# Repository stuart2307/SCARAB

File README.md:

# The SCARAB
The Save and Cartridge Aid Requiring Adapter Boards

# THE IDEA
As far as preservation goes, emphasis is placed on the software side of things.
Tools exist to dump ROMs, and archive them, but there are few tools to diagnose the hardware.
This is the niche the SCARAB aims to fill.

# WHAT DOES IT DO?
It tests the pins of cartridges to ensure they work correctly.
It validates the checksum of the internal ROM.
It tests the save battery, if applicable, via a Save Data Retention test.

# WHY DID YOU MAKE IT?
I've always loved retro gaming, and I am a collector of old hardware.
As such, when given the opportunity to work with it as part of my Final Year Project, I settled on the SCARAB.
I wanted to have some kind of tool to ensure my cartridges were operational.

Licensed under the GNU General Public License.

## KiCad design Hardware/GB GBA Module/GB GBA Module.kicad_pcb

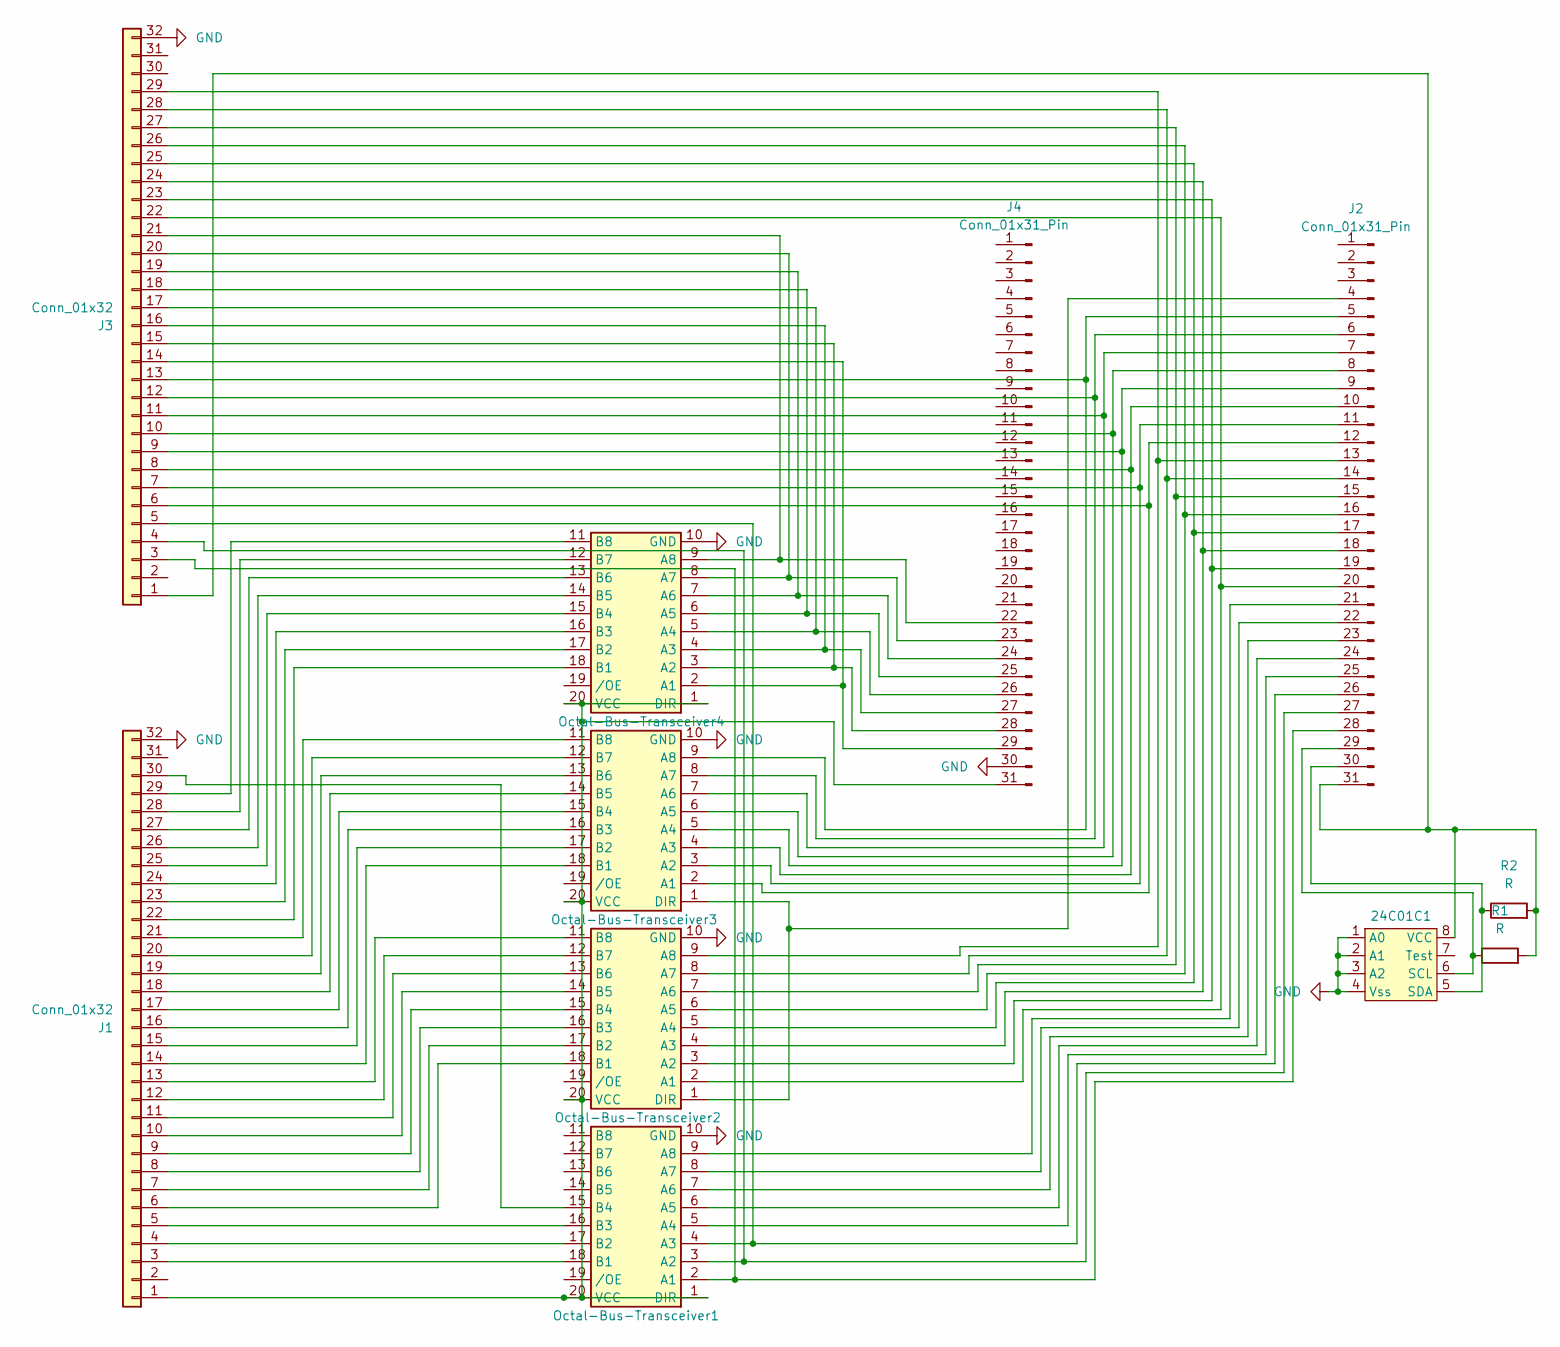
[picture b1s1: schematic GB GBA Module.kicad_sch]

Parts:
24C01C1: DIP-8_W7.62mm
J1, J3: Conn_01x32; GB_GBA_Cartridge_Port
J2, J4: Conn_01x31_Pin; PinSocket_1x31_P2.54mm_Vertical
Octal-Bus-Transceiver1, Octal-Bus-Transceiver2, Octal-Bus-Transceiver3, Octal-Bus-Transceiver4: CERDIP-20_W7.62mm_SideBrazed
R1, R2: R; R_Axial_DIN0207_L6.3mm_D2.5mm_P10.16mm_Horizontal

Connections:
GND: 24C01C1.1 (A0), 24C01C1.2 (A1), 24C01C1.3 (A2), 24C01C1.4 (Vss), J1.32, J3.32, J4.30, Octal-Bus-Transceiver1.10 (GND), Octal-Bus-Transceiver2.10 (GND), Octal-Bus-Transceiver3.10 (GND), Octal-Bus-Transceiver4.10 (GND)
unnamed: 24C01C1.6 (SCL), J2.29, R1.1
unnamed: 24C01C1.5 (SDA), J2.30, R2.1
unnamed: 24C01C1.8 (VCC), J2.31, J3.1, R1.2, R2.2
unnamed: J1.1, J4.31, Octal-Bus-Transceiver1.1 (DIR), Octal-Bus-Transceiver1.20 (VCC), Octal-Bus-Transceiver2.20 (VCC), Octal-Bus-Transceiver3.20 (VCC), Octal-Bus-Transceiver4.1 (DIR), Octal-Bus-Transceiver4.20 (VCC)
unnamed: J1.3, Octal-Bus-Transceiver1.18 (B1)
unnamed: J1.4, Octal-Bus-Transceiver1.17 (B2)
unnamed: J1.5, Octal-Bus-Transceiver1.16 (B3)
unnamed: J1.6, Octal-Bus-Transceiver2.18 (B1)
unnamed: J1.7, Octal-Bus-Transceiver2.17 (B2)
unnamed: J1.8, Octal-Bus-Transceiver2.16 (B3)
unnamed: J1.9, Octal-Bus-Transceiver2.15 (B4)
unnamed: J1.10, Octal-Bus-Transceiver2.14 (B5)
unnamed: J1.11, Octal-Bus-Transceiver2.13 (B6)
unnamed: J1.12, Octal-Bus-Transceiver2.12 (B7)
unnamed: J1.13, Octal-Bus-Transceiver2.11 (B8)
unnamed: J1.14, Octal-Bus-Transceiver3.18 (B1)
unnamed: J1.15, Octal-Bus-Transceiver3.17 (B2)
unnamed: J1.16, Octal-Bus-Transceiver3.16 (B3)
unnamed: J1.17, Octal-Bus-Transceiver3.15 (B4)
unnamed: J1.18, Octal-Bus-Transceiver3.14 (B5)
unnamed: J1.19, Octal-Bus-Transceiver3.13 (B6)
unnamed: J1.20, Octal-Bus-Transceiver3.12 (B7)
unnamed: J1.21, Octal-Bus-Transceiver3.11 (B8)
unnamed: J1.22, Octal-Bus-Transceiver4.18 (B1)
unnamed: J1.23, Octal-Bus-Transceiver4.17 (B2)
unnamed: J1.24, Octal-Bus-Transceiver4.16 (B3)
unnamed: J1.25, Octal-Bus-Transceiver4.15 (B4)
unnamed: J1.26, Octal-Bus-Transceiver4.14 (B5)
unnamed: J1.27, Octal-Bus-Transceiver4.13 (B6)
unnamed: J1.28, Octal-Bus-Transceiver4.12 (B7)
unnamed: J1.29, Octal-Bus-Transceiver4.11 (B8)
unnamed: J1.30, Octal-Bus-Transceiver1.15 (B4)
unnamed: J2.4, Octal-Bus-Transceiver2.1 (DIR), Octal-Bus-Transceiver3.1 (DIR)
unnamed: J2.5, J3.13, Octal-Bus-Transceiver3.9 (A8)
unnamed: J2.6, J3.12, Octal-Bus-Transceiver3.8 (A7)
unnamed: J2.7, J3.11, Octal-Bus-Transceiver3.7 (A6)
unnamed: J2.8, J3.10, Octal-Bus-Transceiver3.6 (A5)
unnamed: J2.9, J3.9, Octal-Bus-Transceiver3.5 (A4)
unnamed: J2.10, J3.8, Octal-Bus-Transceiver3.4 (A3)
unnamed: J2.11, J3.7, Octal-Bus-Transceiver3.3 (A2)
unnamed: J2.12, J3.6, Octal-Bus-Transceiver3.2 (A1)
unnamed: J2.13, J3.29, Octal-Bus-Transceiver2.9 (A8)
unnamed: J2.14, J3.28, Octal-Bus-Transceiver2.8 (A7)
unnamed: J2.15, J3.27, Octal-Bus-Transceiver2.7 (A6)
unnamed: J2.16, J3.26, Octal-Bus-Transceiver2.6 (A5)
unnamed: J2.17, J3.25, Octal-Bus-Transceiver2.5 (A4)
unnamed: J2.18, J3.24, Octal-Bus-Transceiver2.4 (A3)
unnamed: J2.19, J3.23, Octal-Bus-Transceiver2.3 (A2)
unnamed: J2.20, J3.22, Octal-Bus-Transceiver2.2 (A1)
unnamed: J2.21, Octal-Bus-Transceiver1.9 (A8)
unnamed: J2.22, Octal-Bus-Transceiver1.8 (A7)
unnamed: J2.23, Octal-Bus-Transceiver1.7 (A6)
unnamed: J2.24, Octal-Bus-Transceiver1.6 (A5)
unnamed: J2.25, Octal-Bus-Transceiver1.5 (A4)
unnamed: J2.26, J3.5, Octal-Bus-Transceiver1.4 (A3)
unnamed: J2.27, J3.4, Octal-Bus-Transceiver1.3 (A2)
unnamed: J2.28, J3.3, Octal-Bus-Transceiver1.2 (A1)
unnamed: J3.14, J4.29, Octal-Bus-Transceiver4.2 (A1)
unnamed: J3.15, J4.28, Octal-Bus-Transceiver4.3 (A2)
unnamed: J3.16, J4.27, Octal-Bus-Transceiver4.4 (A3)
unnamed: J3.17, J4.26, Octal-Bus-Transceiver4.5 (A4)
unnamed: J3.18, J4.25, Octal-Bus-Transceiver4.6 (A5)
unnamed: J3.19, J4.24, Octal-Bus-Transceiver4.7 (A6)
unnamed: J3.20, J4.23, Octal-Bus-Transceiver4.8 (A7)
unnamed: J3.21, J4.22, Octal-Bus-Transceiver4.9 (A8)

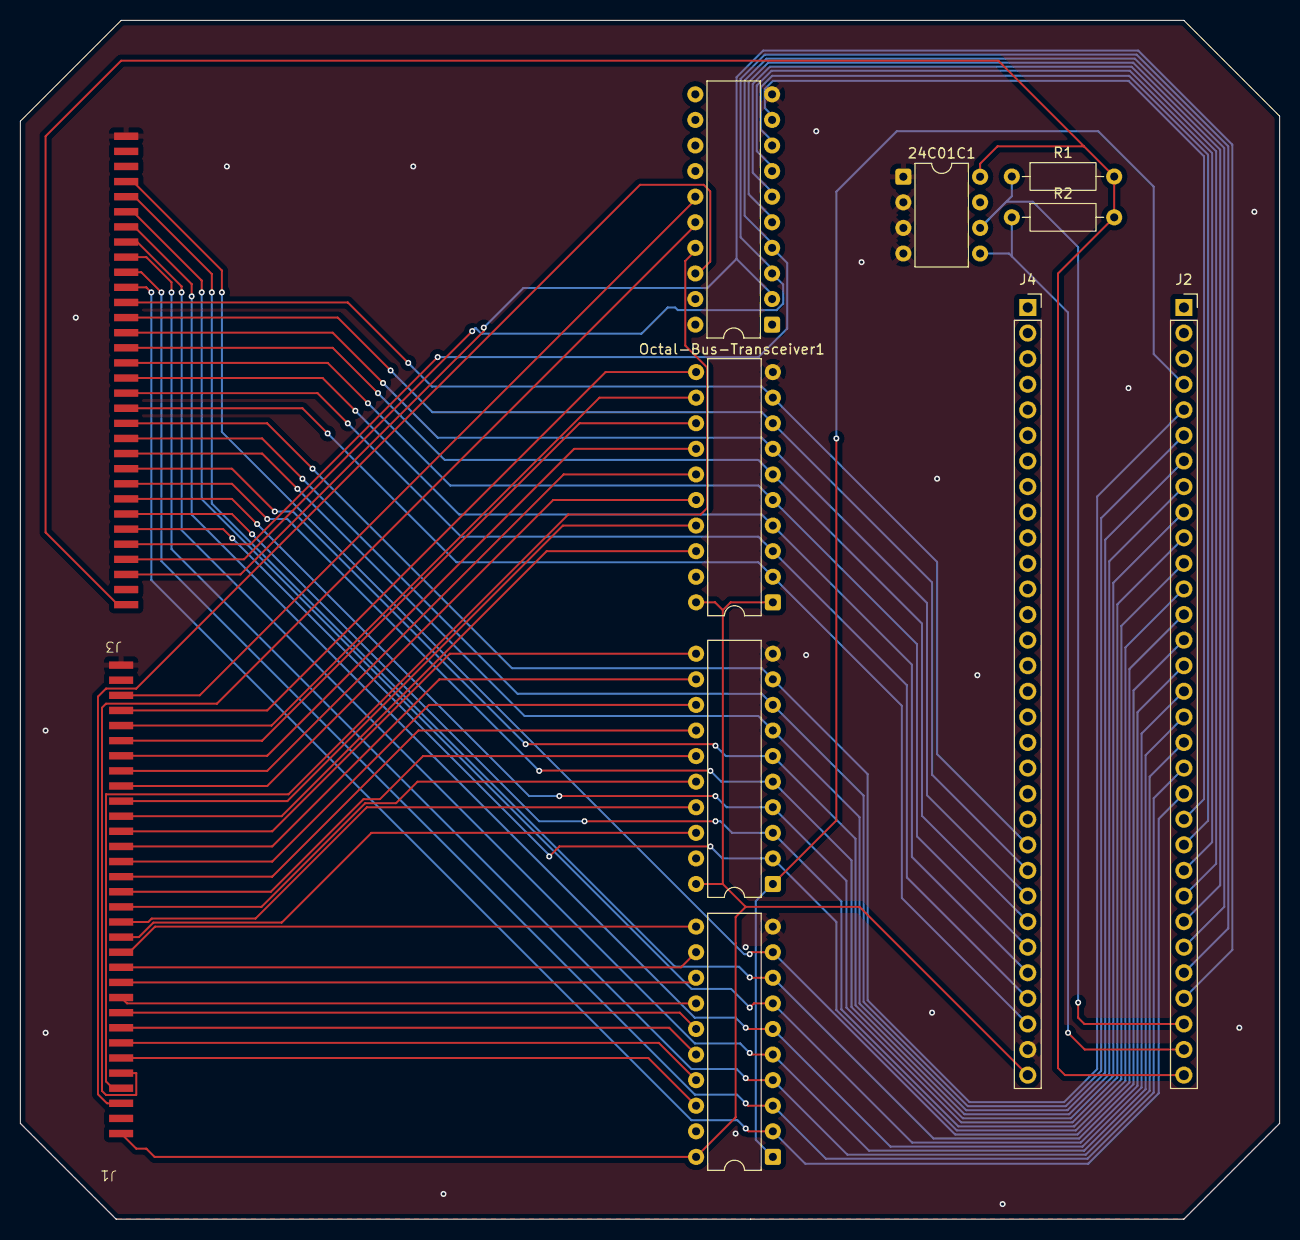
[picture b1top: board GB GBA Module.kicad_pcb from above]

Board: 2 copper layers, 125.0 x 119.0 mm, 11 parts (0 on the bottom side), 66 nets.

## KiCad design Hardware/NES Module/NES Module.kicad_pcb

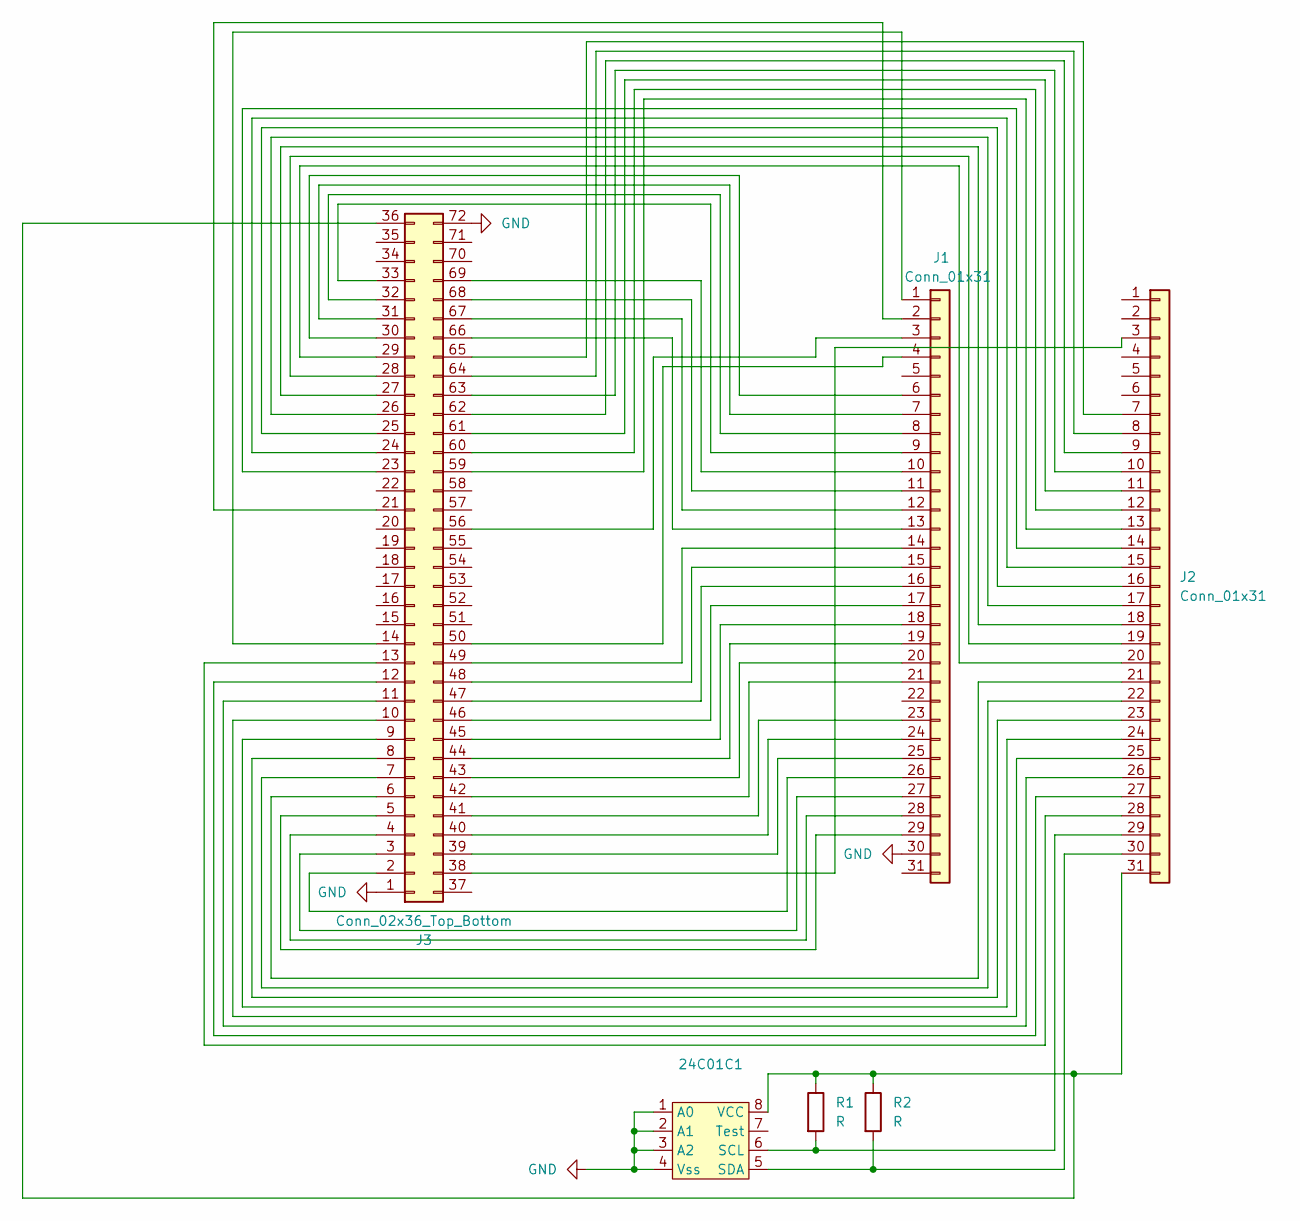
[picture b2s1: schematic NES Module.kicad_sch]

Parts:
24C01C1: DIP-8_W7.62mm
J1, J2: Conn_01x31; PinHeader_1x31_P2.54mm_Vertical
J3: Conn_02x36_Top_Bottom; NES_Cartridge_Port
R1, R2: R; R_Axial_DIN0207_L6.3mm_D2.5mm_P10.16mm_Horizontal

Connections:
GND: 24C01C1.1 (A0), 24C01C1.2 (A1), 24C01C1.3 (A2), 24C01C1.4 (Vss), J1.30, J3.1, J3.72
unnamed: 24C01C1.6 (SCL), J2.29, R1.2
unnamed: 24C01C1.5 (SDA), J2.30, R2.2
unnamed: 24C01C1.8 (VCC), J2.31, J3.36, R1.1, R2.1
unnamed: J1.1, J3.14
unnamed: J1.2, J3.21
unnamed: J1.3, J3.56
unnamed: J1.4, J3.50
unnamed: J1.6, J3.30
unnamed: J1.7, J3.31
unnamed: J1.8, J3.32
unnamed: J1.9, J3.33
unnamed: J1.10, J3.69
unnamed: J1.11, J3.68
unnamed: J1.12, J3.67
unnamed: J1.13, J3.66
unnamed: J1.14, J3.49
unnamed: J1.15, J3.48
unnamed: J1.16, J3.47
unnamed: J1.17, J3.46
unnamed: J1.18, J3.45
unnamed: J1.19, J3.44
unnamed: J1.20, J3.43
unnamed: J1.21, J3.42
unnamed: J1.23, J3.41
unnamed: J1.24, J3.40
unnamed: J1.25, J3.39
unnamed: J1.26, J3.2
unnamed: J1.27, J3.3
unnamed: J1.28, J3.4
unnamed: J1.29, J3.5
unnamed: J2.3, J3.38
unnamed: J2.7, J3.65
unnamed: J2.8, J3.64
unnamed: J2.9, J3.62
unnamed: J2.10, J3.63
unnamed: J2.11, J3.61
unnamed: J2.12, J3.60
unnamed: J2.13, J3.59
unnamed: J2.14, J3.23
unnamed: J2.15, J3.24
unnamed: J2.16, J3.25
unnamed: J2.17, J3.26
unnamed: J2.18, J3.27
unnamed: J2.19, J3.28
unnamed: J2.20, J3.29
unnamed: J2.21, J3.6
unnamed: J2.22, J3.7
unnamed: J2.23, J3.8
unnamed: J2.24, J3.9
unnamed: J2.25, J3.10
unnamed: J2.26, J3.11
unnamed: J2.27, J3.12
unnamed: J2.28, J3.13

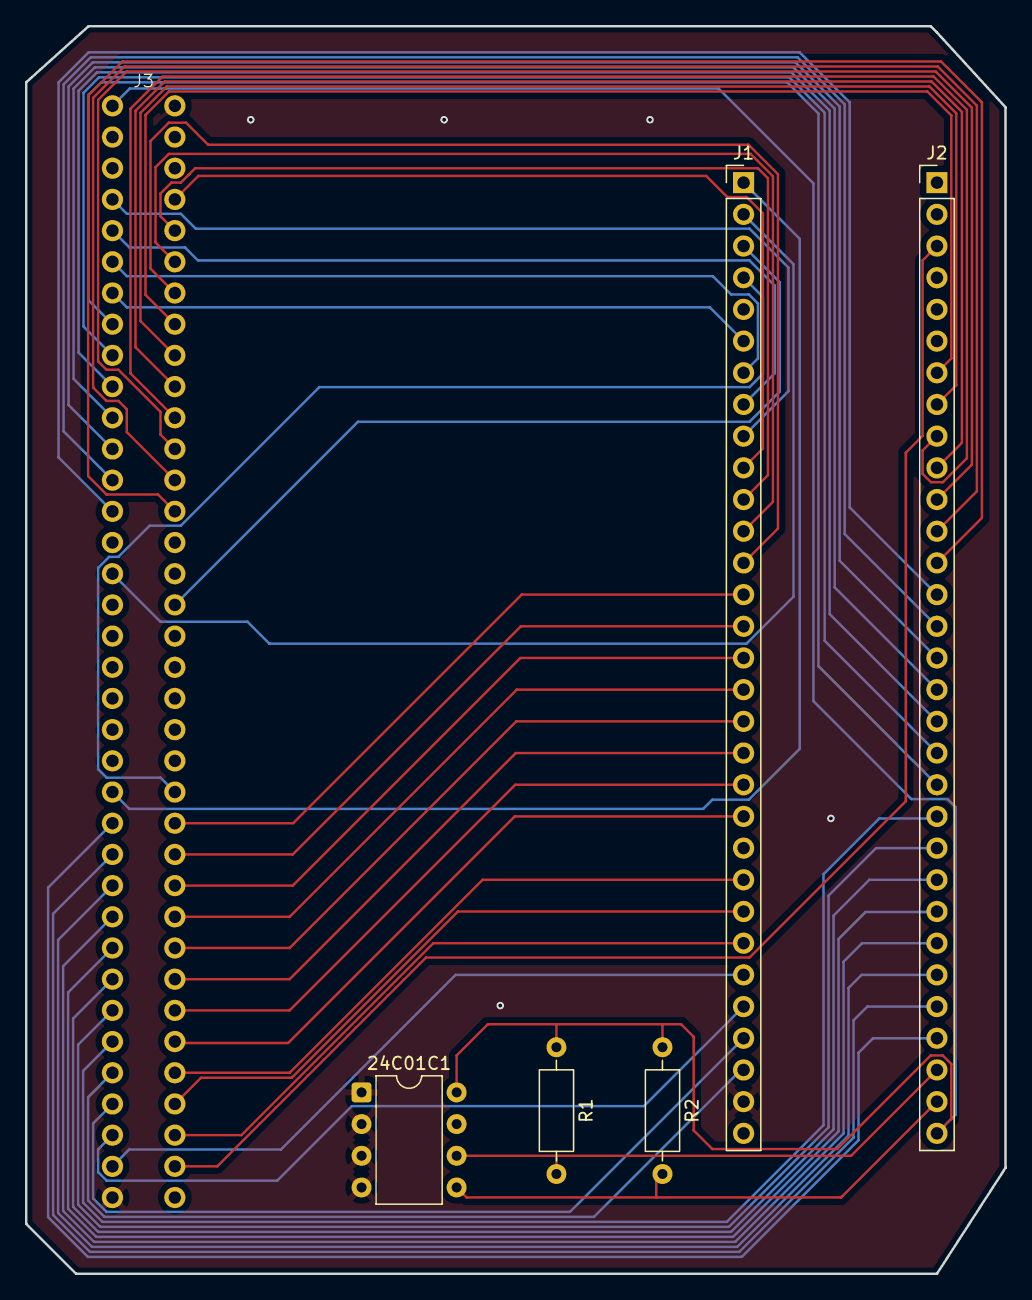
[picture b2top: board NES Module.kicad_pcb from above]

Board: 2 copper layers, 78.5 x 100.0 mm, 6 parts (0 on the bottom side), 54 nets.

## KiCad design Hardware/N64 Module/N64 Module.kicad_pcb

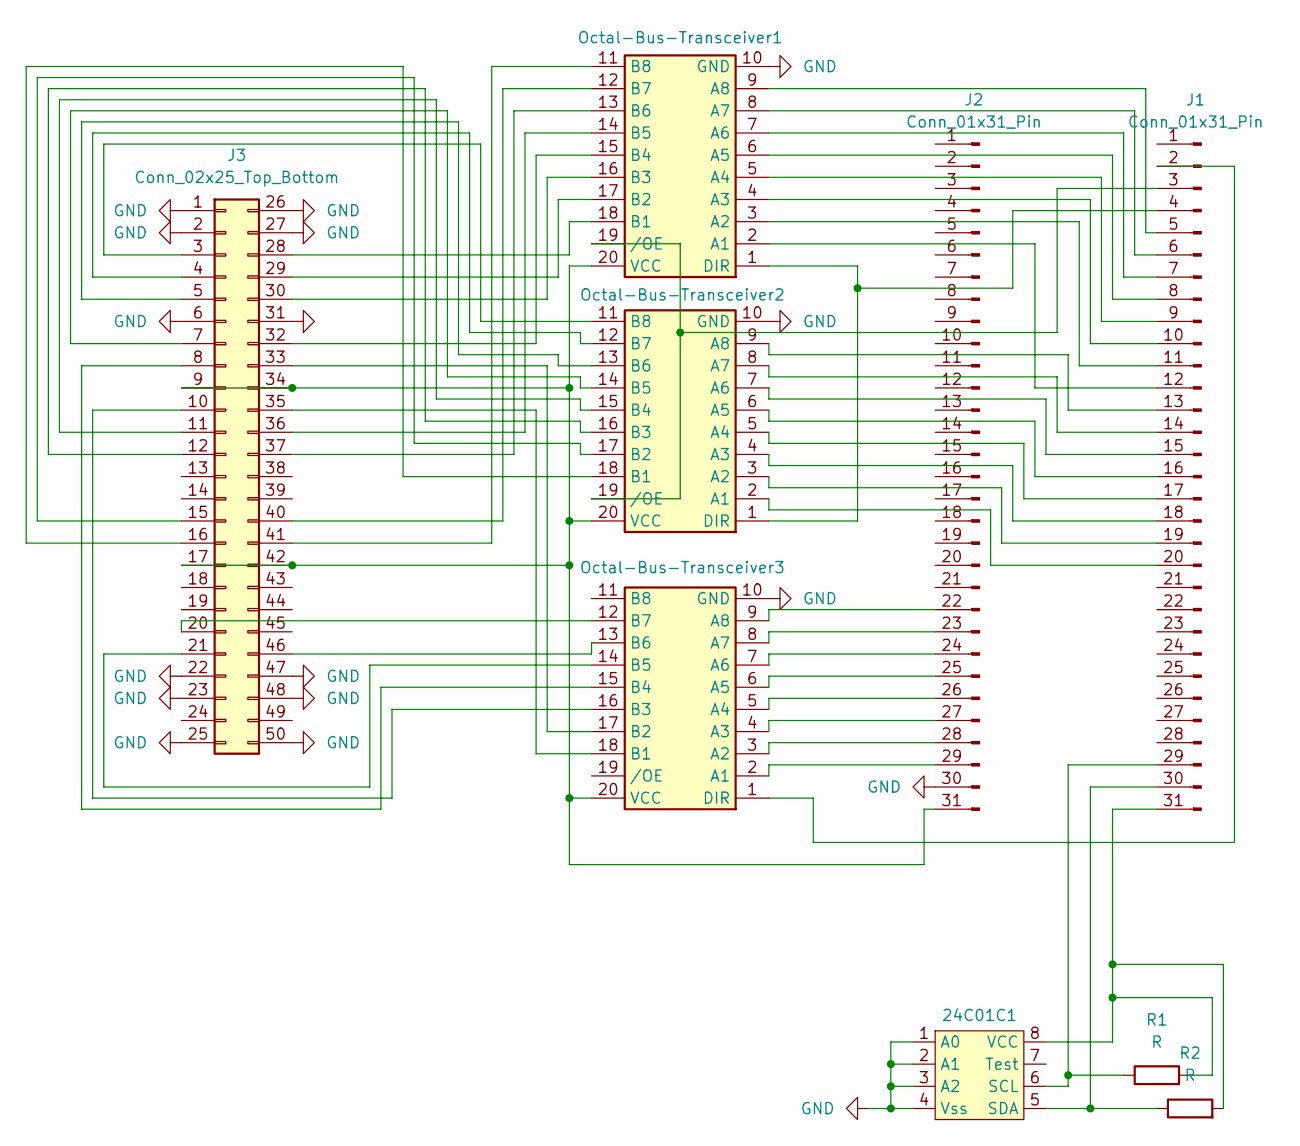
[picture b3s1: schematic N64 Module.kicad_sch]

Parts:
24C01C1: DIP-8_W7.62mm
J1, J2: Conn_01x31_Pin; PinSocket_1x31_P2.54mm_Vertical
J3: Conn_02x25_Top_Bottom; PinHeader_2x25_P2.54mm_Vertical
Octal-Bus-Transceiver1, Octal-Bus-Transceiver2, Octal-Bus-Transceiver3: CERDIP-20_W7.62mm_SideBrazed
R1, R2: R; R_Axial_DIN0207_L6.3mm_D2.5mm_P10.16mm_Horizontal

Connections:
GND: 24C01C1.1 (A0), 24C01C1.2 (A1), 24C01C1.3 (A2), 24C01C1.4 (Vss), J2.30, J3.1, J3.2, J3.6, J3.22, J3.23, J3.25, J3.26, J3.27, J3.31, J3.47, J3.48, J3.50, Octal-Bus-Transceiver1.10 (GND), Octal-Bus-Transceiver2.10 (GND), Octal-Bus-Transceiver3.10 (GND)
unnamed: 24C01C1.6 (SCL), J1.29, R1.1
unnamed: 24C01C1.5 (SDA), J1.30, R2.1
unnamed: 24C01C1.8 (VCC), J1.31, R1.2, R2.2
unnamed: J1.2, Octal-Bus-Transceiver3.1 (DIR)
unnamed: J1.3, Octal-Bus-Transceiver1.19 (/OE), Octal-Bus-Transceiver2.19 (/OE)
unnamed: J1.4, Octal-Bus-Transceiver1.1 (DIR), Octal-Bus-Transceiver2.1 (DIR)
unnamed: J1.5, Octal-Bus-Transceiver1.9 (A8)
unnamed: J1.6, Octal-Bus-Transceiver1.8 (A7)
unnamed: J1.7, Octal-Bus-Transceiver1.7 (A6)
unnamed: J1.8, Octal-Bus-Transceiver1.6 (A5)
unnamed: J1.9, Octal-Bus-Transceiver1.5 (A4)
unnamed: J1.10, Octal-Bus-Transceiver1.4 (A3)
unnamed: J1.11, Octal-Bus-Transceiver1.3 (A2)
unnamed: J1.12, Octal-Bus-Transceiver1.2 (A1)
unnamed: J1.13, Octal-Bus-Transceiver2.9 (A8)
unnamed: J1.14, Octal-Bus-Transceiver2.8 (A7)
unnamed: J1.15, Octal-Bus-Transceiver2.7 (A6)
unnamed: J1.16, Octal-Bus-Transceiver2.6 (A5)
unnamed: J1.17, Octal-Bus-Transceiver2.5 (A4)
unnamed: J1.18, Octal-Bus-Transceiver2.4 (A3)
unnamed: J1.19, Octal-Bus-Transceiver2.3 (A2)
unnamed: J1.20, Octal-Bus-Transceiver2.2 (A1)
unnamed: J2.22, Octal-Bus-Transceiver3.9 (A8)
unnamed: J2.23, Octal-Bus-Transceiver3.8 (A7)
unnamed: J2.24, Octal-Bus-Transceiver3.7 (A6)
unnamed: J2.25, Octal-Bus-Transceiver3.6 (A5)
unnamed: J2.26, Octal-Bus-Transceiver3.5 (A4)
unnamed: J2.27, Octal-Bus-Transceiver3.4 (A3)
unnamed: J2.28, Octal-Bus-Transceiver3.3 (A2)
unnamed: J2.29, Octal-Bus-Transceiver3.2 (A1)
unnamed: J2.31, J3.9, J3.17, J3.34, J3.42, Octal-Bus-Transceiver1.20 (VCC), Octal-Bus-Transceiver2.20 (VCC), Octal-Bus-Transceiver3.20 (VCC)
unnamed: J3.3, Octal-Bus-Transceiver2.11 (B8)
unnamed: J3.4, Octal-Bus-Transceiver2.12 (B7)
unnamed: J3.5, Octal-Bus-Transceiver2.13 (B6)
unnamed: J3.7, Octal-Bus-Transceiver2.14 (B5)
unnamed: J3.8, Octal-Bus-Transceiver3.15 (B4)
unnamed: J3.10, Octal-Bus-Transceiver3.16 (B3)
unnamed: J3.11, Octal-Bus-Transceiver2.15 (B4)
unnamed: J3.12, Octal-Bus-Transceiver2.16 (B3)
unnamed: J3.15, Octal-Bus-Transceiver2.17 (B2)
unnamed: J3.16, Octal-Bus-Transceiver2.18 (B1)
unnamed: J3.20, Octal-Bus-Transceiver3.12 (B7)
unnamed: J3.21, Octal-Bus-Transceiver3.14 (B5)
unnamed: J3.28, Octal-Bus-Transceiver1.18 (B1)
unnamed: J3.29, Octal-Bus-Transceiver1.17 (B2)
unnamed: J3.30, Octal-Bus-Transceiver1.16 (B3)
unnamed: J3.32, Octal-Bus-Transceiver1.15 (B4)
unnamed: J3.33, Octal-Bus-Transceiver3.17 (B2)
unnamed: J3.35, Octal-Bus-Transceiver3.18 (B1)
unnamed: J3.36, Octal-Bus-Transceiver1.14 (B5)
unnamed: J3.37, Octal-Bus-Transceiver1.13 (B6)
unnamed: J3.40, Octal-Bus-Transceiver1.12 (B7)
unnamed: J3.41, Octal-Bus-Transceiver1.11 (B8)
unnamed: J3.46, Octal-Bus-Transceiver3.13 (B6)

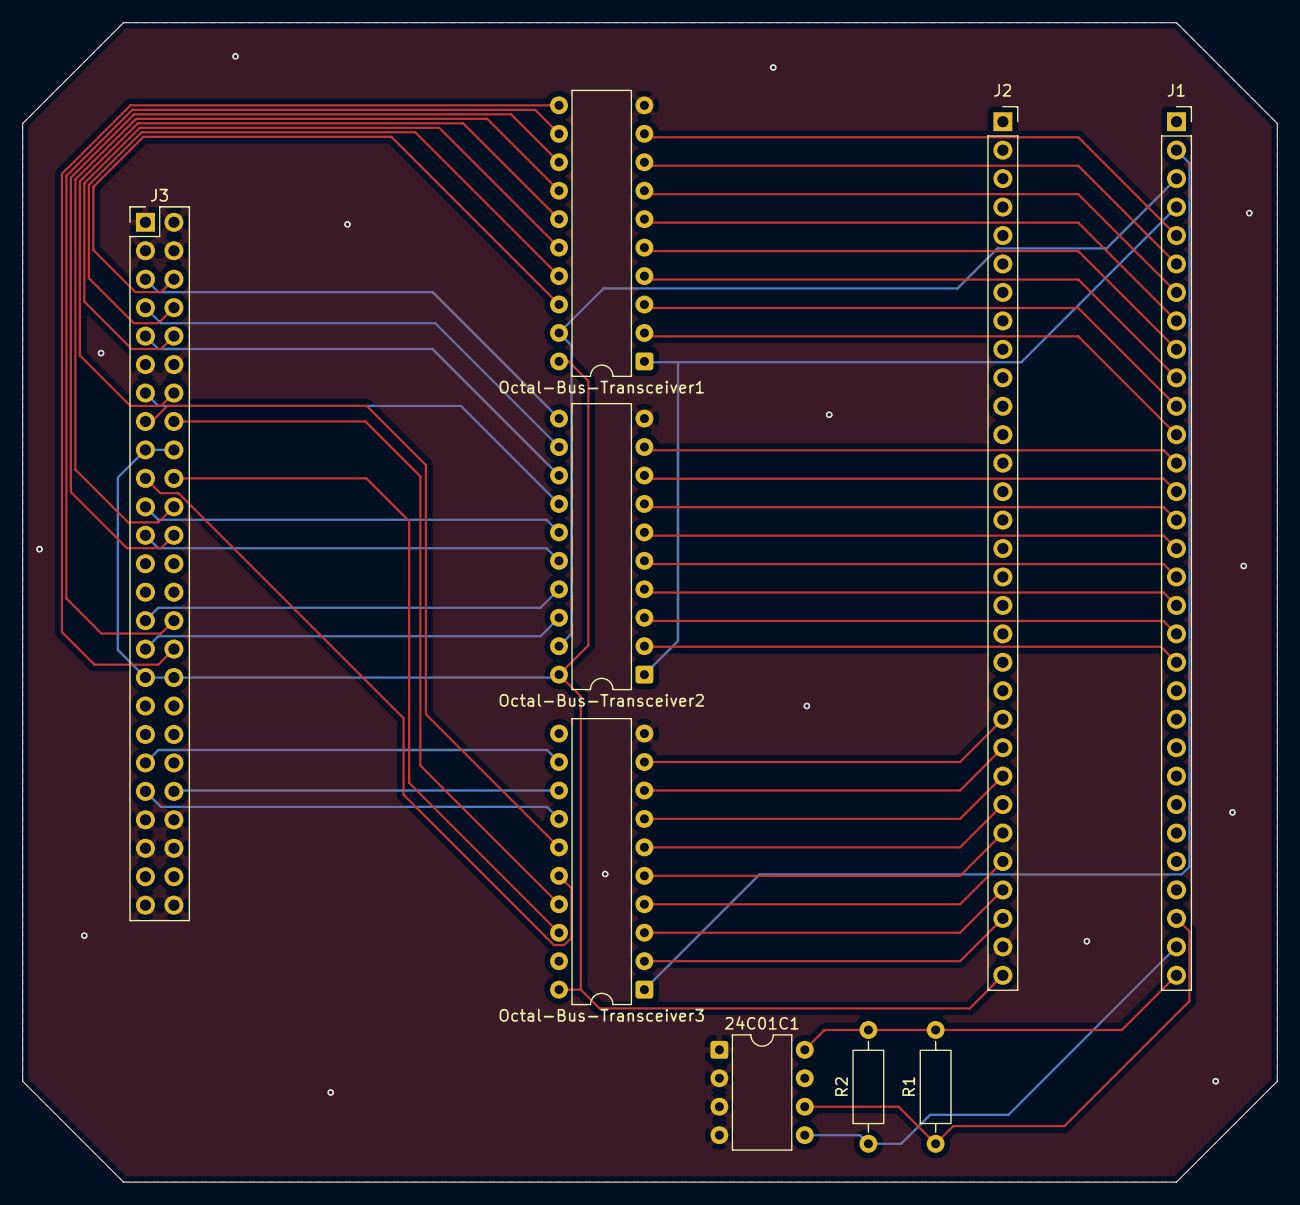
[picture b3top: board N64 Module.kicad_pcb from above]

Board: 2 copper layers, 112.0 x 103.5 mm, 9 parts (0 on the bottom side), 55 nets.

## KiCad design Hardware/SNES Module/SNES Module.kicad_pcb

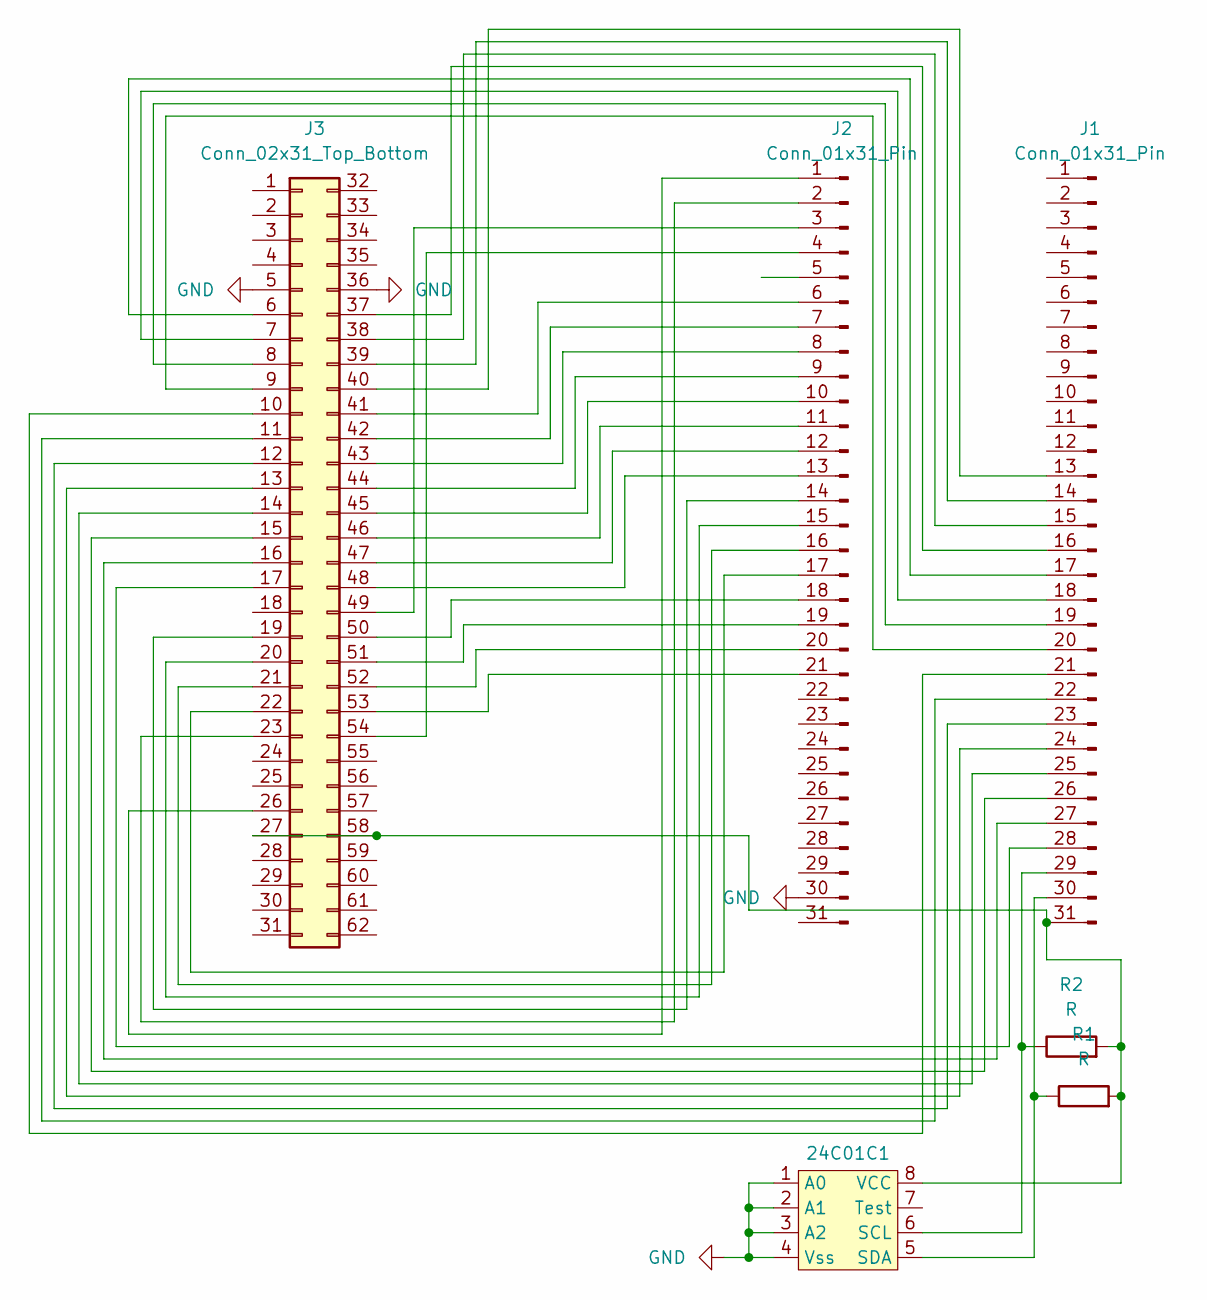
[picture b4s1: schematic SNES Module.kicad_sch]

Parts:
24C01C1: DIP-8_W7.62mm
J1, J2: Conn_01x31_Pin; PinSocket_1x31_P2.54mm_Vertical
J3: Conn_02x31_Top_Bottom; SNES_Cartridge_Port
R1, R2: R; R_Axial_DIN0207_L6.3mm_D2.5mm_P10.16mm_Horizontal

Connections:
GND: 24C01C1.1 (A0), 24C01C1.2 (A1), 24C01C1.3 (A2), 24C01C1.4 (Vss), J2.30, J3.5, J3.36
unnamed: 24C01C1.6 (SCL), J1.29, R2.1
unnamed: 24C01C1.5 (SDA), J1.30, R1.1
unnamed: 24C01C1.8 (VCC), J1.31, J3.27, J3.58, R1.2, R2.2
unnamed: J1.13, J3.40
unnamed: J1.14, J3.39
unnamed: J1.15, J3.38
unnamed: J1.16, J3.37
unnamed: J1.17, J3.6
unnamed: J1.18, J3.7
unnamed: J1.19, J3.8
unnamed: J1.20, J3.9
unnamed: J1.21, J3.10
unnamed: J1.22, J3.11
unnamed: J1.23, J3.12
unnamed: J1.24, J3.13
unnamed: J1.25, J3.14
unnamed: J1.26, J3.15
unnamed: J1.27, J3.16
unnamed: J1.28, J3.17
unnamed: J2.1, J3.26
unnamed: J2.2, J3.23
unnamed: J2.3, J3.49
unnamed: J2.4, J3.54
unnamed: J2.6, J3.41
unnamed: J2.7, J3.42
unnamed: J2.8, J3.43
unnamed: J2.9, J3.44
unnamed: J2.10, J3.45
unnamed: J2.11, J3.46
unnamed: J2.12, J3.47
unnamed: J2.13, J3.48
unnamed: J2.14, J3.19
unnamed: J2.15, J3.20
unnamed: J2.16, J3.21
unnamed: J2.17, J3.22
unnamed: J2.18, J3.50
unnamed: J2.19, J3.51
unnamed: J2.20, J3.52
unnamed: J2.21, J3.53

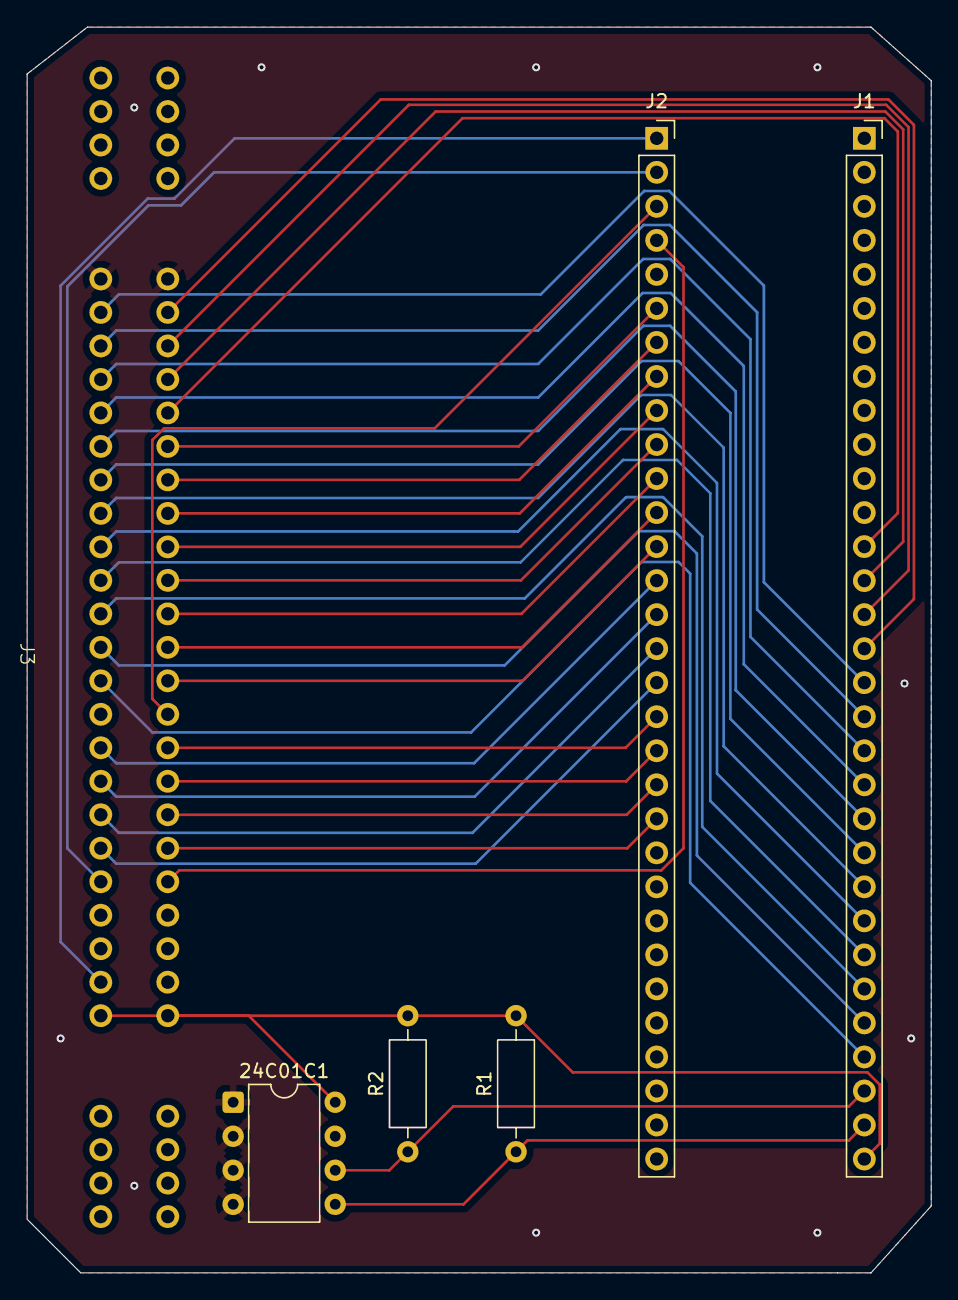
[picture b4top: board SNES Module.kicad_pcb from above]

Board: 2 copper layers, 67.5 x 93.0 mm, 6 parts (0 on the bottom side), 40 nets.

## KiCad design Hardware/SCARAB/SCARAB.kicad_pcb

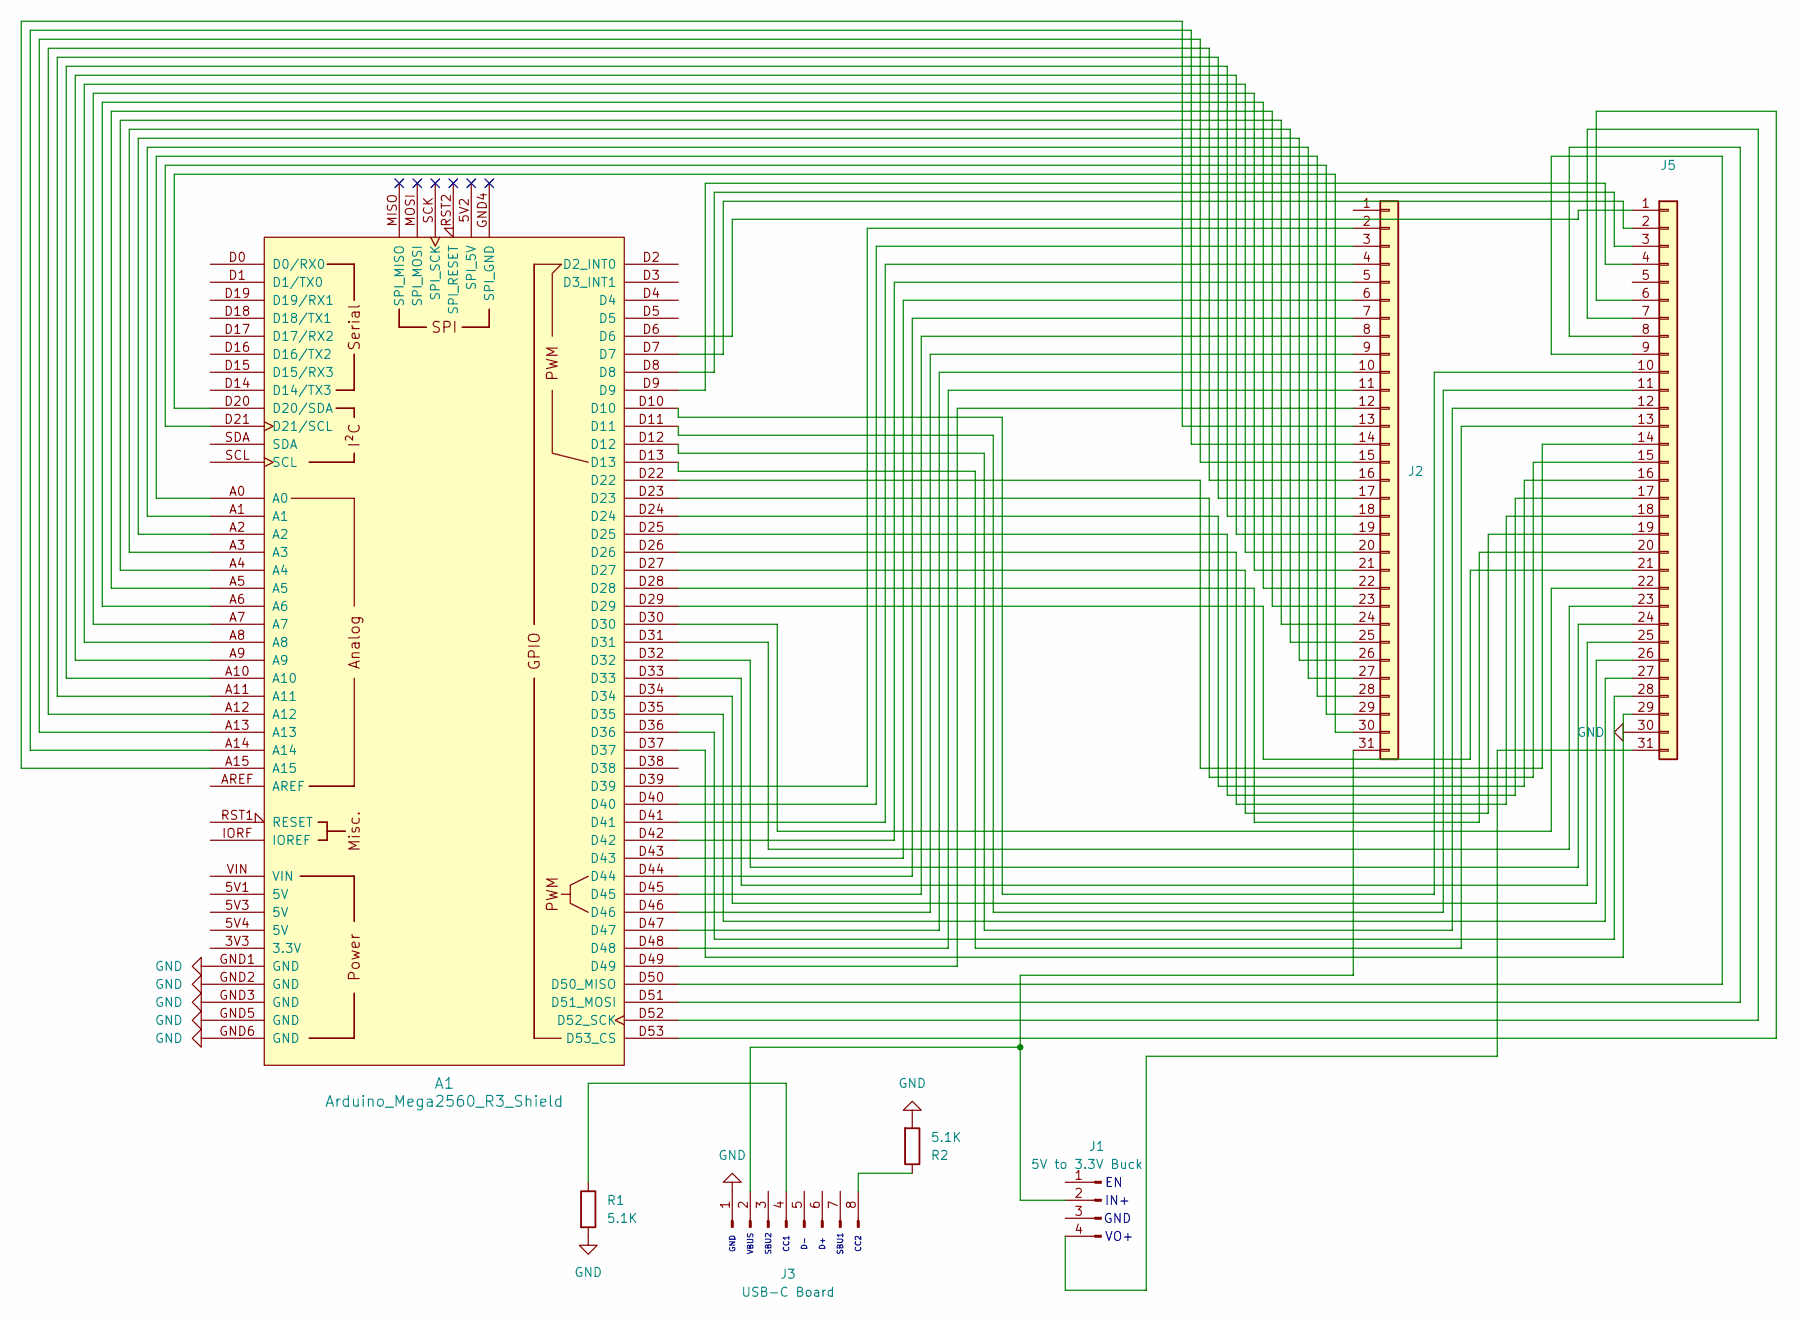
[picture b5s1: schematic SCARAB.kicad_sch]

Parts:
A1: Arduino_Mega2560_R3_Shield
J1: 5V to 3.3V Buck; PinHeader_1x04_P2.54mm_Vertical
J2, J5: Conn_01x31; PinSocket_1x31_P2.54mm_Vertical
J3: USB-C Board; PinSocket_1x08_P2.54mm_Vertical
R1, R2: 5.1K; R_Axial_DIN0207_L6.3mm_D2.5mm_P7.62mm_Horizontal

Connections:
GND: A1.GND1 (GND), A1.GND2 (GND), A1.GND3 (GND), A1.GND5 (GND), A1.GND6 (GND), J3.1, J5.30, R1.2, R2.2
unnamed: A1.D20 (D20/SDA), J2.30
unnamed: A1.D21 (D21/SCL), J2.29
unnamed: A1.D50 (D50_MISO), J5.9
unnamed: A1.D51 (D51_MOSI), J5.8
unnamed: A1.D52 (D52_SCK), J5.7
unnamed: A1.D53 (D53_CS), J5.6
unnamed: J1.2, J2.31, J3.2
unnamed: J1.4, J5.31
unnamed: A1.D39, J2.2
unnamed: A1.D40, J2.3
unnamed: A1.D41, J2.4
unnamed: A1.D42, J2.5
unnamed: A1.D43, J2.6
unnamed: A1.D44, J2.7
unnamed: A1.D45, J2.8
unnamed: A1.D46, J2.9
unnamed: A1.D47, J2.10
unnamed: A1.D48, J2.11
unnamed: A1.D49, J2.12
unnamed: A1.A15, J2.13
unnamed: A1.A14, J2.14
unnamed: A1.A13, J2.15
unnamed: A1.A12, J2.16
unnamed: A1.A11, J2.17
unnamed: A1.A10, J2.18
unnamed: A1.A9, J2.19
unnamed: A1.A8, J2.20
unnamed: A1.A7, J2.21
unnamed: A1.A6, J2.22
unnamed: A1.A5, J2.23
unnamed: A1.A4, J2.24
unnamed: A1.A3, J2.25
unnamed: A1.A2, J2.26
unnamed: A1.A1, J2.27
unnamed: A1.A0, J2.28
unnamed: J3.4, R1.1
unnamed: J3.8, R2.1
unnamed: A1.D6, J5.1
unnamed: A1.D7, J5.2
unnamed: A1.D8, J5.3
unnamed: A1.D9, J5.4
unnamed: A1.D10, J5.10
unnamed: A1.D11, J5.11
unnamed: A1.D12, J5.12
unnamed: A1.D13, J5.13
unnamed: A1.D22, J5.14
unnamed: A1.D23, J5.15
unnamed: A1.D24, J5.16
unnamed: A1.D25, J5.17
unnamed: A1.D26, J5.18
unnamed: A1.D27, J5.19
unnamed: A1.D28, J5.20
unnamed: A1.D29, J5.21
unnamed: A1.D30, J5.22
unnamed: A1.D31, J5.23
unnamed: A1.D32, J5.24
unnamed: A1.D33, J5.25
unnamed: A1.D34, J5.26
unnamed: A1.D35, J5.27
unnamed: A1.D36, J5.28
unnamed: A1.D37, J5.29

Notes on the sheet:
GND VBUS SBU2 CC1 D- D+ SBU1 CC2
GND
VO+
IN+
